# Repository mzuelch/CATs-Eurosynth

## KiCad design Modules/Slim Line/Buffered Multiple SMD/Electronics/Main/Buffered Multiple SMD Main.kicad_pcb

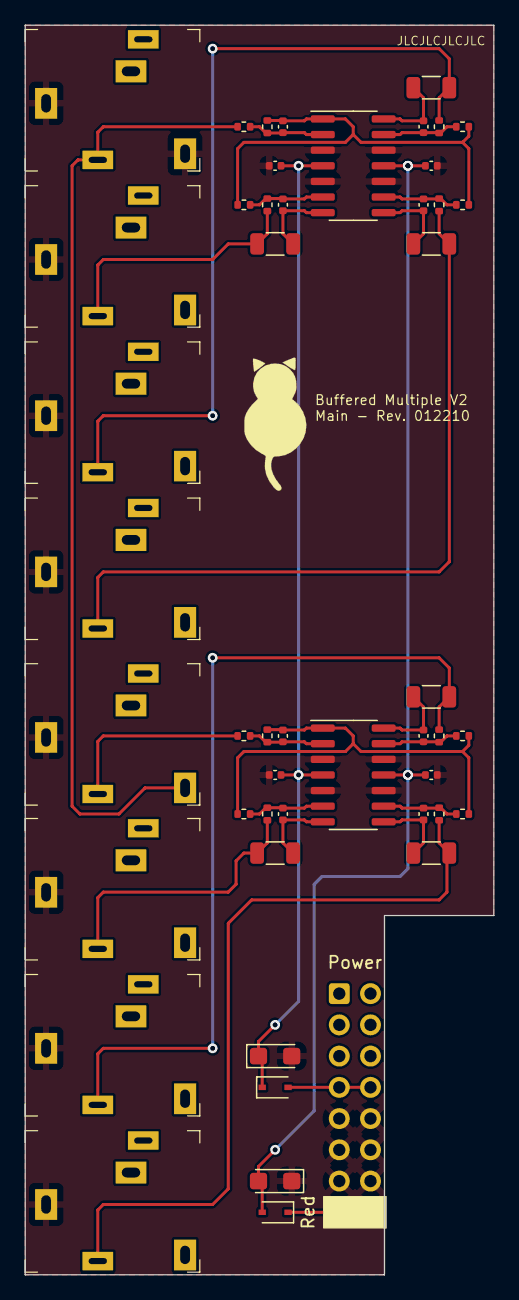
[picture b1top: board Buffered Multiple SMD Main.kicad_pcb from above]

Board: 2 copper layers, 38.1 x 101.6 mm, 49 parts (0 on the bottom side), 29 nets.

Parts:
C1, C2, C3, C4, C5, C6, C7, C8: 10p; C_0402_1005Metric
C9, C12: 10u/16; CP_EIA-3216-18_Kemet-A
C10, C11, C13, C14: 100n; C_0402_1005Metric
D1, D2: 1N5819WS; D_SOD-323
J1: In 1; Jack_3.5mm_QingPu_WQP-PJ324M
J2: In 2; Jack_3.5mm_QingPu_WQP-PJ324M
J3: Out 1-1; Jack_3.5mm_QingPu_WQP-PJ324M
J4: Out 2-1; Jack_3.5mm_QingPu_WQP-PJ324M
J5: Out 1-2; Jack_3.5mm_QingPu_WQP-PJ324M
J6: Out 2-2; Jack_3.5mm_QingPu_WQP-PJ324M
J7: Out 1-3; Jack_3.5mm_QingPu_WQP-PJ324M
J8: Out 2-3; Jack_3.5mm_QingPu_WQP-PJ324M
J9: Power; Power_2x8_Horizontal
R1, R2, R3, R4, R5, R6, R7, R8, R11, R12, R13, R14, R17, R18, R19, R20: 100k; R_0402_1005Metric
R9, R10, R15, R16, R21, R22: 1k; R_1206_3216Metric
U1, U2: TL074CDT; SOIC-14_3.9x8.7mm_P1.27mm

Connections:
+12V: C9.1, C10.2, C11.2, D1.1 (K), U1.4 (V+), U2.4 (V+)
-12V: C12.2, C13.1, C14.1, D2.2 (A), U1.11 (V-), U2.11 (V-)
GND: C9.2, C10.1, C11.1, C12.1, C13.2, C14.2, J1.S, J1.TN, J2.S, J3.S, J4.S, J5.S, J6.S, J7.S, J8.S, J9.GND, U1.3 (+), U1.5 (+), U1.10 (+), U1.12 (+), U2.3 (+), U2.5 (+), U2.10 (+), U2.12 (+)
unnamed: D1.2 (A), J9.+12V
unnamed: D2.1 (K), J9.-12V
unnamed: J1.T, J2.TN, R5.1
unnamed: J2.T, R6.1
unnamed: J3.T, R1.2, R9.2
unnamed: J4.T, R2.2, R10.2
unnamed: J5.T, R11.2, R15.2
unnamed: J6.T, R12.2, R16.2
unnamed: J7.T, R17.2, R21.2
unnamed: J8.T, R18.2, R22.2
unnamed: C1.2, R3.2, R7.1, R13.1, R19.1, U1.1
unnamed: C1.1, R3.1, R5.2, U1.2 (-)
unnamed: C3.1, R1.1, R7.2, U1.6 (-)
unnamed: C3.2, R9.1, U1.7
unnamed: C7.2, R21.1, U1.8
unnamed: C7.1, R17.1, R19.2, U1.9 (-)
unnamed: C5.1, R11.1, R13.2, U1.13 (-)
unnamed: C5.2, R15.1, U1.14
unnamed: C2.2, R4.2, R8.1, R14.1, R20.1, U2.1
unnamed: C2.1, R4.1, R6.2, U2.2 (-)
unnamed: C4.1, R2.1, R8.2, U2.6 (-)
unnamed: C4.2, R10.1, U2.7
unnamed: C8.2, R22.1, U2.8
unnamed: C8.1, R18.1, R20.2, U2.9 (-)
unnamed: C6.1, R12.1, R14.2, U2.13 (-)
unnamed: C6.2, R16.1, U2.14

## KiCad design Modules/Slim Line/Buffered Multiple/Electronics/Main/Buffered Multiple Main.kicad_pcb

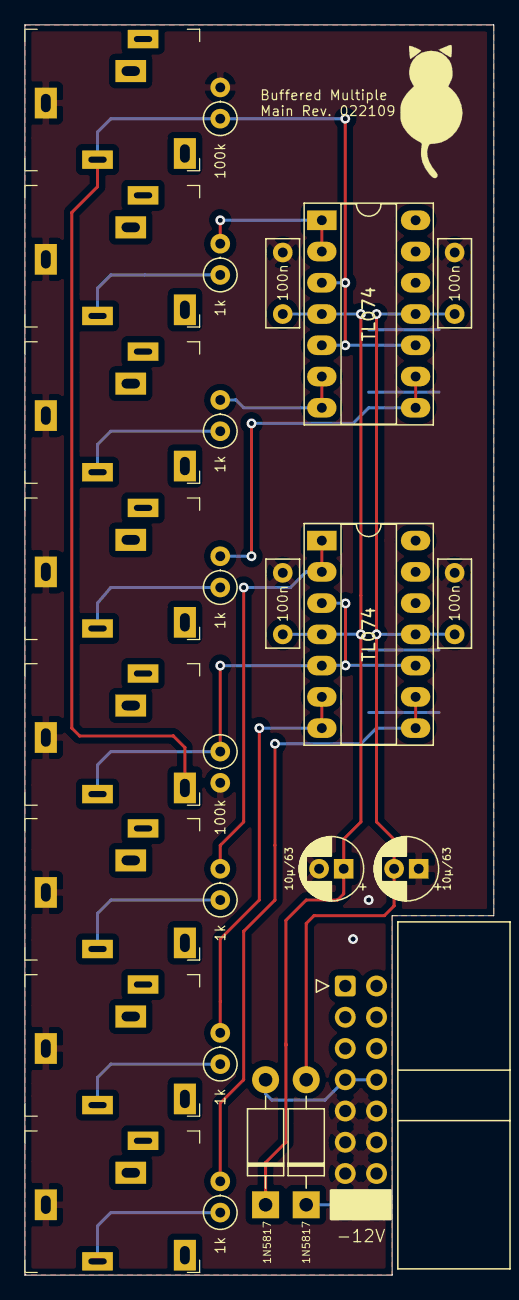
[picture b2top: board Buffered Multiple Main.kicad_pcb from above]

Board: 2 copper layers, 38.1 x 101.6 mm, 27 parts (0 on the bottom side), 19 nets.

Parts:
C1, C2: 10µ/63; CP_Radial_D5.0mm_P2.00mm
C3, C4, C5, C6: 100n; C_Rect_L7.0mm_W2.5mm_P5.00mm
D1, D2: 1N5817; D_DO-41_SOD81_P10.16mm_Horizontal
J1: In 1; Jack_3.5mm_QingPu_WQP-PJ324M
J2: Power; IDC-Header_2x08_P2.54mm_Horizontal
J3: Out 1-1; Jack_3.5mm_QingPu_WQP-PJ324M
J4: Out 1-2; Jack_3.5mm_QingPu_WQP-PJ324M
J5: Out 2-1; Jack_3.5mm_QingPu_WQP-PJ324M
J6: Out 2-2; Jack_3.5mm_QingPu_WQP-PJ324M
J7: In 2; Jack_3.5mm_QingPu_WQP-PJ324M
J8: Out 1-3; Jack_3.5mm_QingPu_WQP-PJ324M
J9: Out 2-3; Jack_3.5mm_QingPu_WQP-PJ324M
R1, R6: 100k; R_Axial_DIN0207_L6.3mm_D2.5mm_P2.54mm_Vertical
R2, R3, R4, R5, R7, R8: 1k; R_Axial_DIN0207_L6.3mm_D2.5mm_P2.54mm_Vertical
U1, U2: TL074; DIP-14_W7.62mm_Socket_LongPads

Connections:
+12V: C1.1, C3.1, C5.1, D1.1, U1.4, U2.4
+12VA: D1.2, J2.7, J2.8
-12V: C2.2, C4.2, C6.2, D2.2, U1.11, U2.11
-12VA: D2.1, J2.15, J2.16
GND: C1.2, C2.1, C3.2, C4.1, C5.2, C6.1, J1.S, J2.9, J2.10, J2.11, J2.12, J2.13, J2.14, J3.S, J4.S, J5.S, J6.S, J7.S, J8.S, J9.S, R1.2, R6.2
unnamed: J1.T, J7.TN, R1.1, U1.3, U1.5, U1.10
unnamed: J3.T, R2.1
unnamed: J4.T, R3.1
unnamed: J5.T, R4.1
unnamed: J6.T, R5.1
unnamed: J7.T, R6.1, U2.3, U2.5, U2.10
unnamed: J8.T, R7.1
unnamed: J9.T, R8.1
unnamed: R2.2, U1.1, U1.2
unnamed: R3.2, U1.6, U1.7
unnamed: R4.2, U2.1, U2.2
unnamed: R5.2, U2.6, U2.7
unnamed: R7.2, U1.8, U1.9
unnamed: R8.2, U2.8, U2.9

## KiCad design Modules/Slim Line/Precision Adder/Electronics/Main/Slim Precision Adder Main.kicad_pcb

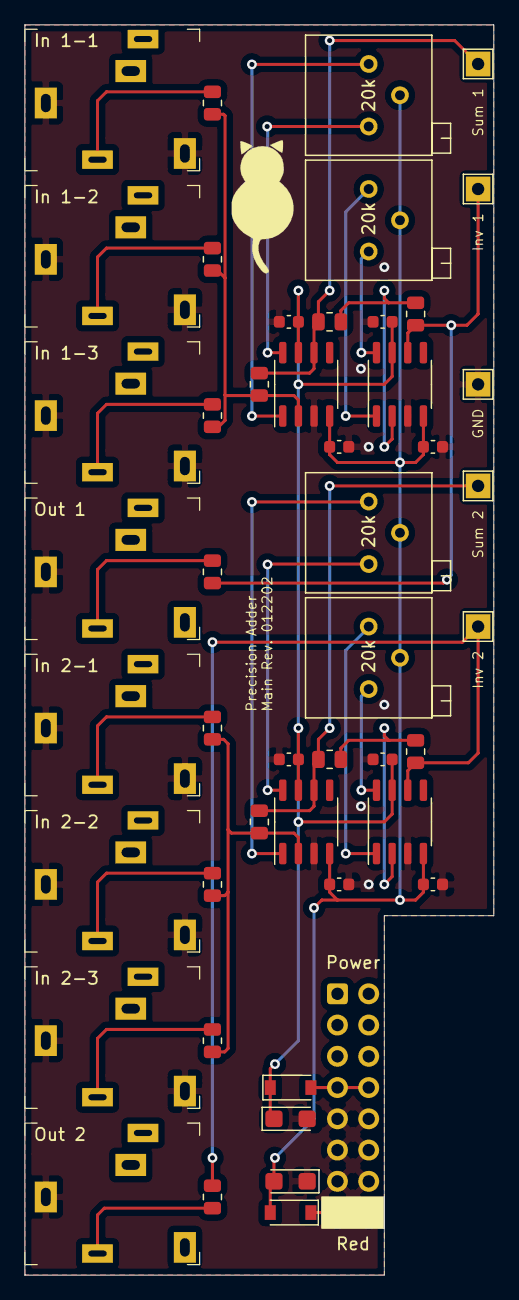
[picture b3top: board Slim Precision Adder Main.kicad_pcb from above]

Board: 2 copper layers, 38.1 x 101.6 mm, 48 parts (0 on the bottom side), 29 nets.

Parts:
C1, C6: 10u; CP_EIA-3216-18_Kemet-A
C2, C3, C4, C5, C7, C8, C9, C10: 100n; C_0603_1608Metric
D1, D2: B5819W SL; D_SOD-123
J1: In 1-1; Jack_3.5mm_QingPu_WQP-PJ324M
J2: Out 1; Jack_3.5mm_QingPu_WQP-PJ324M
J3: In 1-2; Jack_3.5mm_QingPu_WQP-PJ324M
J4: In 1-3; Jack_3.5mm_QingPu_WQP-PJ324M
J5: In 2-1; Jack_3.5mm_QingPu_WQP-PJ324M
J6: Out 2; Jack_3.5mm_QingPu_WQP-PJ324M
J7: In 2-2; Jack_3.5mm_QingPu_WQP-PJ324M
J8: In 2-3; Jack_3.5mm_QingPu_WQP-PJ324M
J9: Power; Power_2x8_Horizontal
R1, R2, R3, R5, R6, R7, R8, R9, R10, R12, R13, R14: 100k ±0.05%; R_0805_2012Metric
R4, R11: 240; R_0805_2012Metric
RV1, RV2, RV3, RV4: 20k; Potentiometer_Bourns_3299P_Horizontal
TP1: Inv 1; TestPoint_THTPad_2.0x2.0mm_Drill1.0mm
TP2: Sum 1; TestPoint_THTPad_2.0x2.0mm_Drill1.0mm
TP3: GND; TestPoint_THTPad_2.0x2.0mm_Drill1.0mm
TP4: Inv 2; TestPoint_THTPad_2.0x2.0mm_Drill1.0mm
TP5: Sum 2; TestPoint_THTPad_2.0x2.0mm_Drill1.0mm
U1, U2, U3, U4: OP07CDR; SO-8_3.9x4.9mm_P1.27mm

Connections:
+12V: C1.1, C2.1, C3.1, C4.1, C5.1, D1.1, U1.7, U2.7, U3.7, U4.7
-12V: C6.2, C7.2, C8.2, C9.2, C10.2, D2.2, RV1.2, RV2.2, RV3.2, RV4.2, U1.4, U2.4, U3.4, U4.4
GND: C1.2, C2.2, C3.2, C4.2, C5.2, C6.1, C7.1, C8.1, C9.1, C10.1, J1.S, J1.TN, J2.S, J3.S, J3.TN, J4.S, J4.TN, J5.S, J5.TN, J6.S, J7.S, J7.TN, J8.S, J8.TN, J9.GND, TP3.1, U1.3, U2.3, U3.3, U4.3
unnamed: D1.2, J9.+12V
unnamed: D2.1, J9.-12V
unnamed: J1.T, R3.2
unnamed: J2.T, R4.1
unnamed: J3.T, R6.2
unnamed: J4.T, R7.2
unnamed: J5.T, R10.2
unnamed: J6.T, R11.1
unnamed: J7.T, R13.2
unnamed: J8.T, R14.2
unnamed: R1.1, R4.2, TP1.1, U1.6
unnamed: R1.2, R5.1, U1.2
unnamed: R2.1, R5.2, TP2.1, U2.6
unnamed: R2.2, R3.1, R6.1, R7.1, U2.2
unnamed: R9.2, R10.1, R13.1, R14.1, U4.2
unnamed: R8.1, R11.2, TP4.1, U3.6
unnamed: R8.2, R12.1, U3.2
unnamed: R9.1, R12.2, TP5.1, U4.6
unnamed: RV1.1, U1.8
unnamed: RV1.3, U1.1
unnamed: RV2.1, U2.8
unnamed: RV2.3, U2.1
unnamed: RV3.1, U3.8
unnamed: RV3.3, U3.1
unnamed: RV4.1, U4.8
unnamed: RV4.3, U4.1

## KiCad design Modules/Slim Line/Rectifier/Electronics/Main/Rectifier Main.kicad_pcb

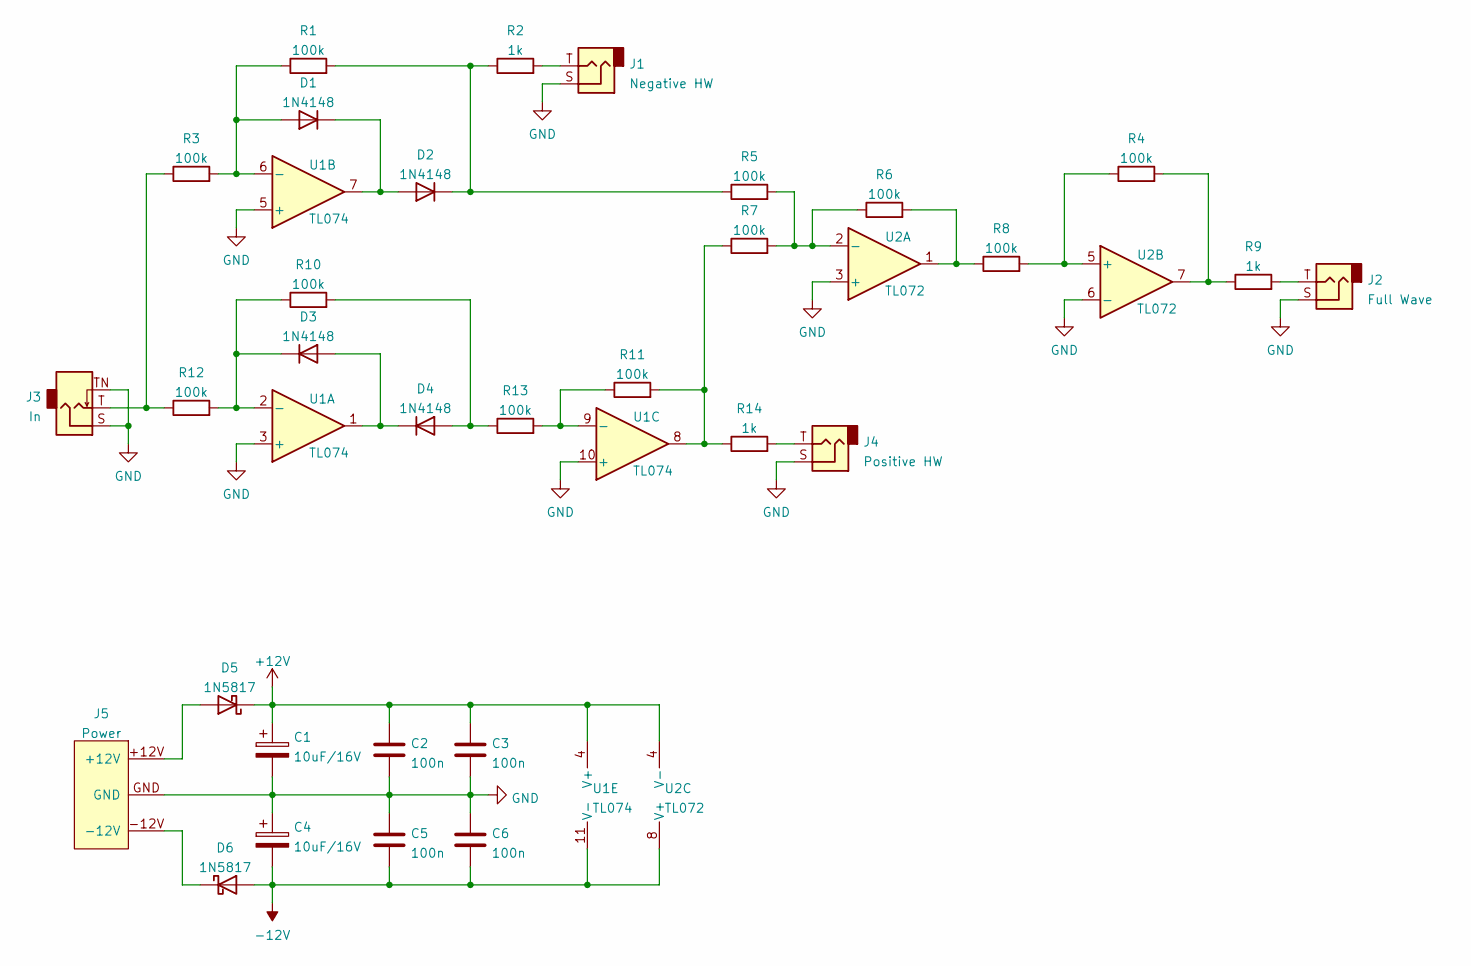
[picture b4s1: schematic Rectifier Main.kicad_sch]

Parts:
C1, C4: 10uF/16V; CP_Radial_D5.0mm_P2.00mm
C2, C3, C5, C6: 100n; C_Disc_D4.3mm_W1.9mm_P5.00mm
D1, D2, D3, D4: 1N4148; D_DO-35_SOD27_P7.62mm_Horizontal
D5, D6: 1N5817; D_DO-41_SOD81_P10.16mm_Horizontal
J1: Negative HW; Jack_3.5mm_QingPu_WQP-PJ324M
J2: Full Wave; Jack_3.5mm_QingPu_WQP-PJ324M
J3: In; Jack_3.5mm_QingPu_WQP-PJ324M
J4: Positive HW; Jack_3.5mm_QingPu_WQP-PJ324M
J5: Power; Power_2x8_Horizontal
R1, R3, R4, R5, R6, R7, R8, R10, R11, R12, R13: 100k; R_Axial_DIN0207_L6.3mm_D2.5mm_P7.62mm_Horizontal
R2, R9, R14: 1k; R_Axial_DIN0207_L6.3mm_D2.5mm_P7.62mm_Horizontal
U1: TL074; DIP-14_W7.62mm_LongPads
U2: TL072; DIP-8_W7.62mm_LongPads

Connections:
+12V: C1.1, C2.1, C3.1, D5.1 (K), U1.4 (V+), U2.4 (V-)
-12V: C4.2, C5.2, C6.2, D6.2 (A), U1.11 (V-), U2.8 (V+)
GND: C1.2, C2.2, C3.2, C4.1, C5.1, C6.1, J1.S, J2.S, J3.S, J3.TN, J4.S, J5.GND, U1.3 (+), U1.5 (+), U1.10 (+), U2.3 (+), U2.6 (-)
unnamed: D1.1 (K), D2.2 (A), U1.7
unnamed: D1.2 (A), R1.1, R3.2, U1.6 (-)
unnamed: D2.1 (K), R1.2, R2.1, R5.1
unnamed: D3.1 (K), R10.1, R12.2, U1.2 (-)
unnamed: D3.2 (A), D4.1 (K), U1.1
unnamed: D4.2 (A), R10.2, R13.1
unnamed: D5.2 (A), J5.+12V
unnamed: D6.1 (K), J5.-12V
unnamed: J1.T, R2.2
unnamed: J2.T, R9.2
unnamed: J3.T, R3.1, R12.1
unnamed: J4.T, R14.2
unnamed: R4.1, R8.2, U2.5 (+)
unnamed: R4.2, R9.1, U2.7
unnamed: R5.2, R6.1, R7.2, U2.2 (-)
unnamed: R6.2, R8.1, U2.1
unnamed: R11.1, R13.2, U1.9 (-)
unnamed: R7.1, R11.2, R14.1, U1.8

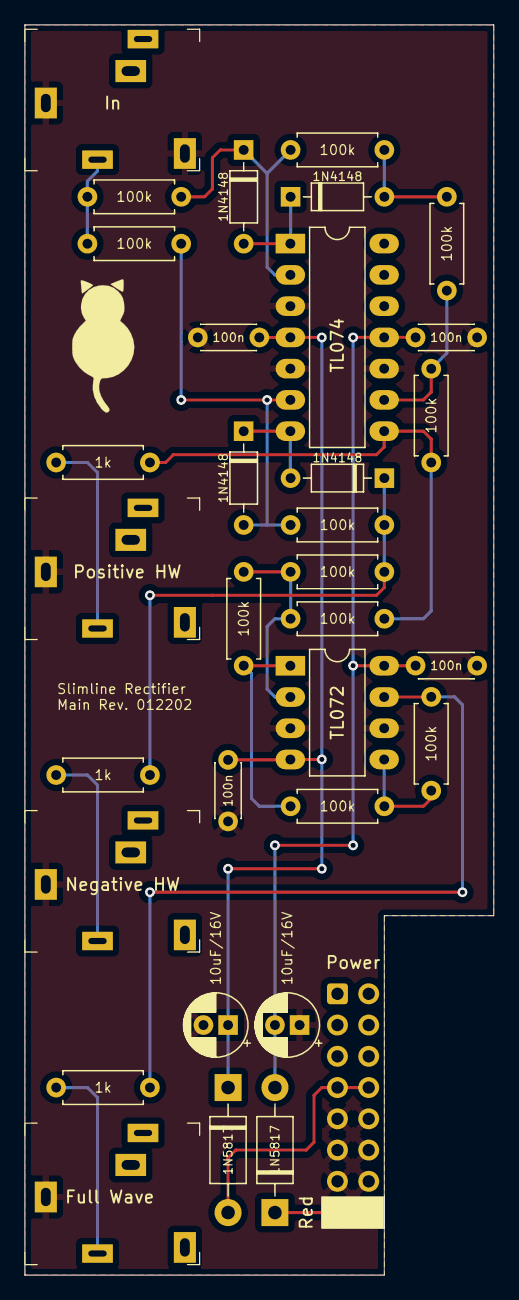
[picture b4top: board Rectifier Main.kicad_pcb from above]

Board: 2 copper layers, 38.1 x 101.6 mm, 33 parts (0 on the bottom side), 21 nets.
